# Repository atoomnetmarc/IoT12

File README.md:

# Hi!

This is an attempt at creating a soldering iron controller that uses T12 tips for a soldering iron handle with GX12-5 connector (KSGER FX9501 Handle). The pinout of the GX12-5 connector should match [this table](#control-board-j5-to-gx12-5-connector).

The name IoT12 is a portmanteau of IoT (because this soldering iron controller is connected to the internet using WiFi) and T12 (the type of soldering iron tip).

Have a look at the different elements that make up this project:

- [3d models for the case](3d/)
- [firmware for the heat controller and main processor](firmware/)
- [schematic and pcb](hardware/)

# Status

**Experimental and incomplete. Do not replicate yet.**

**You should be present at all times when using this project in case something goes wrong.**

# Assembly

You will need to 3d print all the parts mentioned in [3d](3d/README.md) directory.

You will need the 3 PCBs mentioned in the [hardware](hardware/README.md) directory.

# Cable harness

You need to crimp some JST-XH connectors and an IDC cable. Except for the IDC cable, use a wire diameter that can carry 3A. I used 0.2mm² (24 AWG, RS PRO series stranded tinned copper conductor equipment wire with PVC insulation).

## Power supply J2 to power switch

Cut 2 pieces of 14cm (5 33/64 inch) wire and crimp JST-XH pin on 1 end. Then plug into JST-XHP-2 connector. Solder the other end to a 16mm round rocker switch.

| Pin   | Description       | Wire color    |
| --:   | --                | --            |
| 1     | To power switch   | Purple        |
| 2     | To power switch   | Purple        |

## Power supply J3 to Control Board J4

Cut 4 pieces of 14cm wire and crimp JST-XH pin on both ends. Then plug into JST-XHP-4 connector.

| Pin   | Description   | Wire color    |
| --:   | --            | --            |
| 1     | +24V          | Yellow        |
| 2     | +5V           | Red           |
| 3     | GND           | Black         |
| 4     | +24V ON       | Pink          |

## Control board J2 to speaker

Cut 2 pieces of 14cm wire and crimp JST-XH pin on 1 end. Then plug into JST-XHP-2 connector. Solder the other end to a 4cm speaker (4 ohm 3 watt)

| Pin   | Description       | Wire color    |
| --:   | --                | --            |
| 1     | To speaker        | Brown         |
| 2     | To speaker        | Brown         |

## Control board J5 to GX12-5 connector

Cut 5 pieces of 14cm wire and crimp JST-XH pin on 1 end. Then plug into JST-XHP-52 connector. Solder other end to GX12-5 connector.

| Pin   | Description       | Wire color    |
| --:   | --                | --            |
| 1     | shake             | Blue          |
| 2     | NTC               | White         |
| 3     | ESD               | Green         |
| 4     | T12-              | Black         |
| 5     | T12+              | Red           |

## Control board J1 to Display Adapter J1

Cut a 14 cm 14-pin 1.27mm pitch ribbon cable. Crimp a IDC-14 connector on both ends. You should orient both connectors so that one polarizing key points away from the center of the cable and the other points to the center of the cable. Please note that pin 1 of the cable should align with pin 1 on both connectors (indicated by a triangle on the connector).

# Testing

Connect a (KSGER) T12 solder iron handle with the T12 tip (really) firmly seated inside to the GX12-5 socket. The JST-XH connector should connected to the control pcb. The power supply board should be connected to to the control pcb, but not powered on.

Measure about 60kΩ between the tip of the iron and GND on the control board (J6).

Measure 1MΩ between the tip of the iron and EARTH pin at the Power supply board (J1).

Now measure some values at the solder iron connector J5.\
The heater resistor between 4 (black) and 5 (red): 8Ω.\
Not 8Ω? Now retry and really push in the T12 tip into the handle.

Switch over to measure mV and measure 4 (black) and 5 (red) again. When you have not touched the handle and tip for half an hour you should read 0mV. Grab the cold T12 tip with your hand. You should notice an increasing voltage, possibly a rise until 0.1mV. It is possible your voltmeter is not capable of measuring in the microvolt range. You can heat the tip with a flame for a few seconds to increase the voltage some more.

Measure the NTC between 4 (black) and 2 (white): 5KΩ at 22°C (71.6°F) room temperature, but resistance could vary slightly when not measuring at 22°C.

Test the tilt sensor. Point soldering iron up and measure between 1 (blue) and 3 (green). You are measuring around 250kΩ.\
Point iron down and measure a low resistance of less than 100Ω.

The soldering iron handle is now validated to be correctly connected and should function correctly.

Connect the speaker to J2 on the control board.

Connect the power switch to J2 on the power supply board.

Connect display adapter J1 to control board J1.

Modules A1 and A3 should not be plugged in yet. All other connectors are plugged in.

Apply current limited (100mA) 24V with your lab power supply to the right leg of F1 on the power supply board (and gnd on some other pin like the middle pin of U1). Apply the 24V slowly starting at 0V. Stop at 6V. Measure the 5V pin on J4 (it should be 5.2V), notice LED D4 also lit up. Continue increasing to 24V. Current should stay below 10mA. Turn off lab power supply.

When all tests went well flash [the firmware](firmware/README.md) to both A1 (ESP32) and A3 (SAMD21). Do not plug in the modules in the control board before flashing the firmware.

Plug in A1 and A3. Both USB connectors should point to the center of the control board.
Again apply current limited 24V. But now increase the limit to 250mA. At about 6V the display should turn on. Both blue LEDs on A3 and the red LED on A3 should also light up. Current is now about 200mA. Increase until 24V. Current is now about 60mA.\
Measure the 3V3 pin on J6, it should measure 3.3V.

If your power supply can handle 3.5A at 24V you could try enable heating of the soldering iron. To enable heating you must switch on the power switch connected to J2 on the power supply board.

If you came this far and all tests went well, go reward yourself with your favorite drink or snack. Happy.

# Final assembly

\<insert final assembly instructions here, something about fitting everything in the 3d printed case, hmm, maybe this is all the instuctions needed>

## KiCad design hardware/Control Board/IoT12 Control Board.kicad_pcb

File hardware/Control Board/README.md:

# Assembly instructions

Use the [interactive BOM](bom/ibom.html) to identify values and positions of the components.

Solder all small 0805 SMD resistors and capacitors.
Read special instructions for R60, R61 and R62, R63 in the schematic.

Measure all resistors and check if they are all the correct resistance.

Solder rest of SMD components.

Clean PCB.

Inspect PCB with microscope for shorted pins (in ICs). Correct when found.

Solder all through-hole components.

Clean PCB.

You now have something like this:

Apply current limited 5V to GND and +5V on J4. Almost no current should flow.

Apply current limited 3.3V to GND and 3V3 on J6. Almost no current should flow.

# Done

Done!

# Pinout J1, Board-to-board Display

Connector to the Display Adapter. Direction seen from the control board.

| Pin# | Description | Direction |
| ---- | ----------- | --------- |
| 1    | +3.3V       | Power     |
| 2    | TFT_DC      | Out       |
| 3    | GND         | Power     |
| 4    | TFT_SCLK    | Out       |
| 5    | GND         | Power     |
| 6    | TFT_MOSI    | Out       |
| 7    | GND         | Power     |
| 8    | TFT_MISO    | In        |
| 9    | GND         | Power     |
| 10   | TFT_CS      | Out       |
| 11   | TFT_LED     | Out       |
| 12   | TFT_RST     | Out       |
| 13   | TOUCH_CS    | Out       |
| 14   | TOUCH_IRQ   | In        |

# Pinout J2, Speaker

Spoken soldering instructions for the visually impaired.

| Pin # | Description |
| ----- | ----------- |
| 1     | Loudspeaker |
| 2     | Loudspeaker |

# Pinout J4, Board-to-board Power

Goes to power board.

| Pin # | Description        |
| ----- | ------------------ |
| 1     | 24V switched power |
| 2     | 5V always on       |
| 3     | GND                |
| 4     | 24V_ON             |

# Pinout J5, T12 soldering iron

| Pin # | Description                      |
| ----- | -------------------------------- |
| 1     | SHAKE_IN                         |
| 2     | NTC_IN                           |
| 3     | ESD, connected with 100KΩ to GND |
| 4     | IRON\_-                          |
| 5     | IRON\_+                          |

# Pinout J6, Expansion I/O

Expansion connector, wired to the SAMD21 (EXP_D5, EXP_D7, EXP_SCL, EXP_SDA). Currently unused.

| Pin # | Description |
| ----- | ----------- |
| 1     | EXP_D5      |
| 2     | EXP_D7      |
| 3     | EXP_SCL     |
| 4     | EXP_SDA     |
| 5     | +3.3V       |
| 6     | GND         |

# Pinout A1, ESP32

The wireless brains.

| GPIO # | Description | Direction |
| ------ | ----------- | --------- |
| EN     | ESP32_RESET | In        |
| IO32   | TFT_LED     | Out       |
| IO33   | I2S_SD      | Out       |
| IO25   | I2S_BCK     | Out       |
| IO26   | I2S_WS      | Out       |
| IO21   | ESP32_SDA   | Bidir     |
| IO22   | ESP32_SCL   | Out       |
| IO14   | I2S_GAIN1   | Out       |
| IO13   | I2S_GAIN0   | Out       |
| IO15   | TFT_CS      | Out       |
| IO2    | TFT_DC      | Out       |
| IO4    | TFT_RST     | Out       |
| IO5    | TOUCH_CS    | Out       |
| IO18   | TFT_SCLK    | Out       |
| IO19   | TFT_MISO    | In        |
| IO23   | TFT_MOSI    | Out       |
| IO27   | I2S_DATA    | Out       |
| IO34   | TOUCH_IRQ   | In        |
| IO35   | HEAT_INT    | In        |

# Pinout A3, SAMD21

Heater controller

| GPIO #    | Description  | Direction |
| --------- | ------------ | --------- |
| RESET     | SAMD21_RESET | In        |
| PA02      | NTC          | In        |
| PB08      | TEMP         | In        |
| PB09+PA04 | SHAKE        | In        |
| PA05      | VIN          | In        |
| PB02      | IRON_CURRENT | In        |
| PA14      | HEAT_INT     | Out       |
| PA15      | EXP_D5       | Bidir     |
| PA20      | FLASH_CS     | Out       |
| PA21      | EXP_D7       | Bidir     |
| PA06      | ADC_RDY      | In        |
| PA07      | 24V_ON       | Out       |
| PA18      | HEAT_PWM     | Out       |
| PA22      | HEAT_SDA     | Bidir     |
| PA23      | HEAT_SCL     | Out       |
| PA08      | ESP32_SDA    | Bidir     |
| PA09      | ESP32_SCL    | In        |
| PA16      | EXP_SDA      | Bidir     |
| PA17      | EXP_SCL      | Out       |
| PA12      | MISO         | In        |
| PB11      | SCK          | Out       |
| PB10      | MOSI         | Out       |

# Pinout U2, ADS1115

16b I2C ADC, I2C address 0x48, on the HEAT I2C bus.

| Pin # | Pin name  | Description  | Direction |
| ----- | --------- | ------------ | --------- |
| 1     | ADDR      | GND          | In        |
| 2     | ALERT/RDY | ADC_RDY      | Out       |
| 3     | GND       | NEAR_ADC_GND | In        |
| 4     | AIN0      | TEMP         | In        |
| 5     | AIN1      | NTC          | In        |
| 6     | AIN2      | IRON_CURRENT | In        |
| 7     | AIN3      | VIN          | In        |
| 8     | VDD       | +3.3V        | In        |
| 9     | SDA       | HEAT_SDA     | Bidir     |
| 10    | SCL       | HEAT_SCL     | In        |

# Changelog

**Control board PCB version V2.2**

- Removed debug LED
- Removed 5110 LCD
- Removed rotary encoder
- Added header for 2.8" ILI9341 320x240 touch TFT
- Added relay for switching 24V
- Moved power supply circuitry to power supply PCB
- Removed small EEPROM
- Added SPI flash
- Added expansion header
- Layed out PCB again to fit on bottom lid of enclosure

**Control board PCB version V2.1**

- Swapped SDA/SCL I2C minion pins on heater controller.
- Swapped SDA/SCL I2C master pins on heater controller.
- Renamed PWM_HEAT to HEAT_PWM.
- Re-added MAX809S voltage monitor to keep ESP32 in reset if 3.3V is too low.
- Dimensioned F1 to 50% of Amax of T12-tip, see notes in schematic.
- Connected Vin ADC to after F1.
- Moved USB connector and reset button of heater controller.

**Control board PCB version V2.0**

- Replace safety features by microcontroller.
- Heating control now done by microcontroller.
- Changed shape and layout of pcb.

**Control board PCB version V1.1**

- Added explanation to schematic about using matched resistors for the instrumentation amplifiers.
- Changed gain resistors of the instrumentation amplifiers as to keep Vout under 1V at full scale input.
- Added series diode to output of voltage monitor.
- Lowered value of C2-C5 from 10nF to 1nF.
- Added D9 and D10.
- Changed value of R9 from 100R to 1k
- Added circuit to shutdown heating in case of overheating tip.

**Control board PCB version V1.0**

- First version that got made into PCB form.

# Eratta

**Control board PCB version V2.2**

No known erratum.

**Control board PCB version V2.1**

- It seems that after some use the 5110 LCD module has unreliable contacts. The LCD should be replaced by something else. PCB will need to be redesigned.
- A single occurrence of incorrect and fluctuating temperatures has been observed. Possibly caused by arcs in the power switch during power on. The power switch needs te be replaced by something else. Also the firmware needs to be made aware somehow of the situation and shutdown heating.

**Control board PCB version V2.0**

- I2C to heater controller not working. SDA/SCL are swapped. Swap them on the PCB near R55 and R56 to make the ESP32 communicate to the heater controller.
- A theme is developing :unamused:. I2C from the heater controller to the I2C EEPROM and ADC is not working. SDA/SCL are swapped. Swap them between R53, R54 and the heater controller on the bottom where the SDA/SCL traces run next to each other.
- ESP32 will lockup if power supply rise time is too slow.

**Control board PCB version V1.1**

- Overheating protection circuit not very stable. No fix.

**Control board PCB version V1.0**

- Silkscreen error in 'Solder iron connector'-block. '5, red, +.' and '4, black, ground.' are switched resulting in negative voltages for positive temperatures. Switch leads will solve this. Corrected in next PCB version.
- Gain of instrumentation amplifiers not correct.
- Programming by USB is impossible.
- Measuring temperature takes too long (20ms).

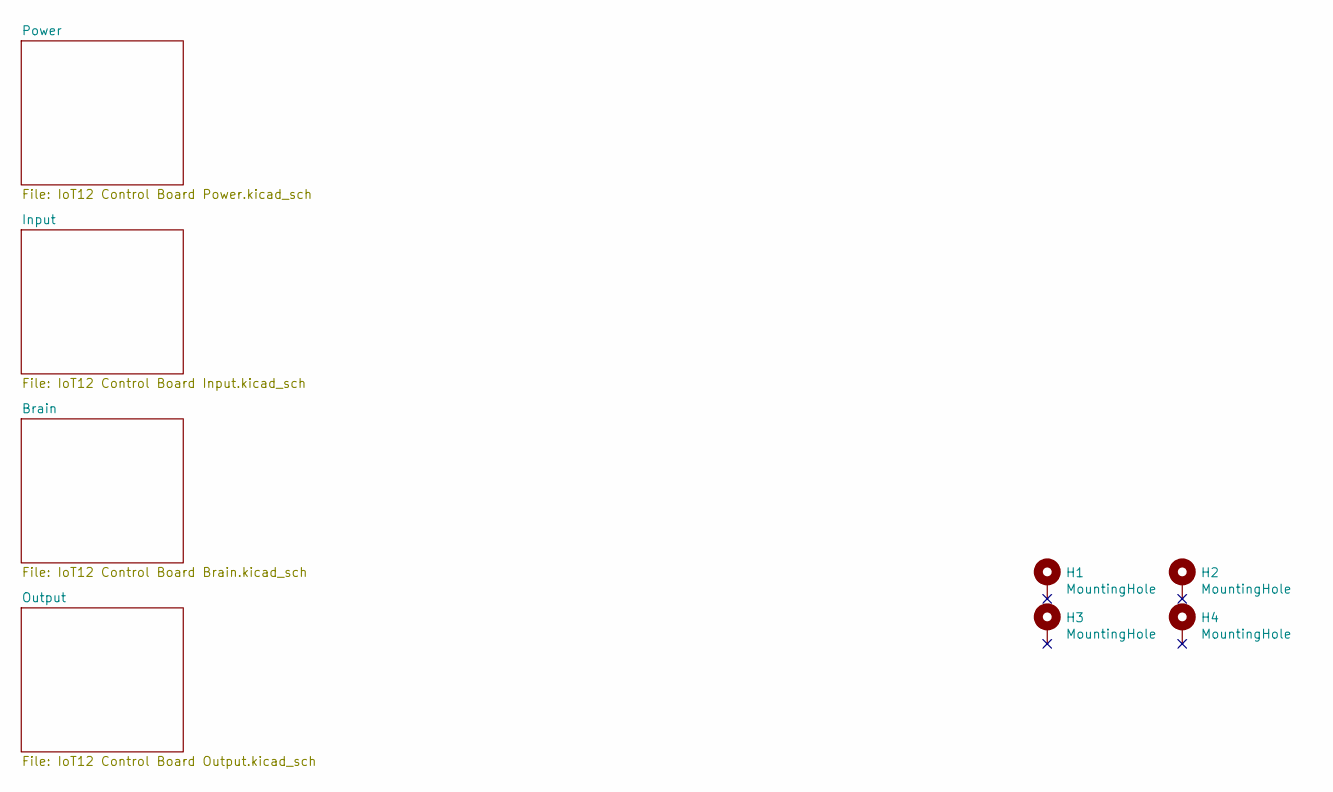
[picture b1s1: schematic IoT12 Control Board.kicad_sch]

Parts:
H1, H2, H3, H4: MountingHole; MountingHole_3.2mm_M3_Pad_Via

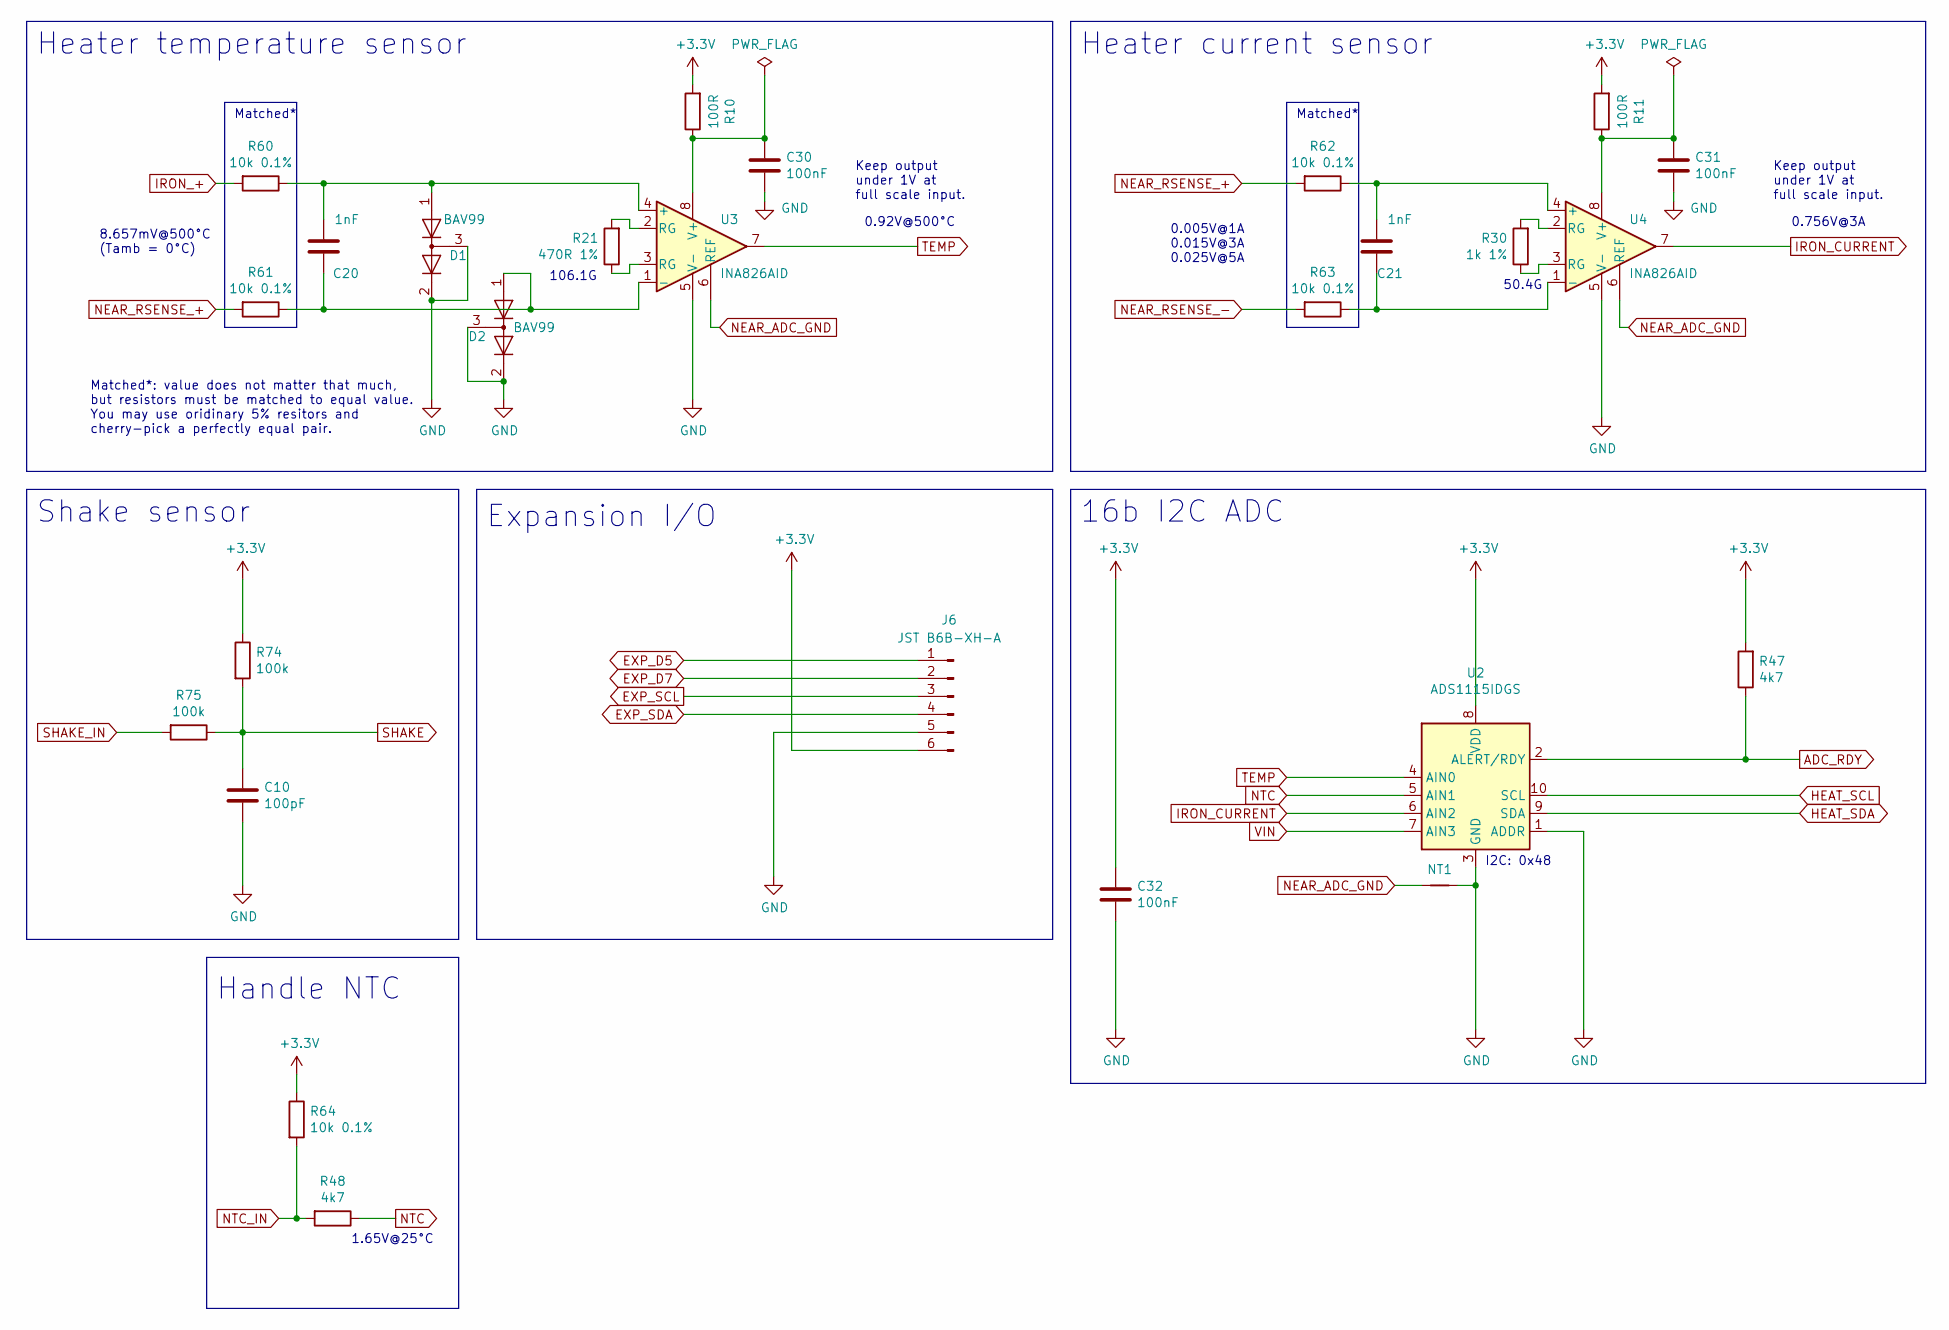
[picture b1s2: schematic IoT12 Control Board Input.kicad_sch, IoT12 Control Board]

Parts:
C10: 100pF; C_0805_2012Metric_Pad1.18x1.45mm_HandSolder
C20, C21: 1nF; C_0805_2012Metric_Pad1.18x1.45mm_HandSolder
C30, C31, C32: 100nF; C_0805_2012Metric_Pad1.18x1.45mm_HandSolder
D1, D2: BAV99; SOT-23
J6: JST B6B-XH-A; JST_XH_B6B-XH-A_1x06_P2.50mm_Vertical
NT1: NetTie-2_SMD_Pad0.5mm
R10, R11: 100R; R_0805_2012Metric_Pad1.20x1.40mm_HandSolder
R21: 470R 1%; R_0805_2012Metric_Pad1.20x1.40mm_HandSolder
R30: 1k 1%; R_0805_2012Metric_Pad1.20x1.40mm_HandSolder
R47, R48: 4k7; R_0805_2012Metric_Pad1.20x1.40mm_HandSolder
R60, R61, R62, R63, R64: 10k 0.1%; R_0805_2012Metric_Pad1.20x1.40mm_HandSolder
R74, R75: 100k; R_0805_2012Metric_Pad1.20x1.40mm_HandSolder
U2: ADS1115IDGS; TSSOP-10_3x3mm_P0.5mm
U3, U4: INA826AID; SOIC-8_5.23x5.23mm_P1.27mm

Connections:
+3.3V: C32.1, J6.6, R10.2, R11.2, R47.2, R64.1, R74.1, U2.8 (VDD); also elsewhere on the board
ADC_RDY: R47.1, U2.2 (ALERT/RDY); also elsewhere on the board
EXP_D5: J6.1; also elsewhere on the board
EXP_D7: J6.2; also elsewhere on the board
EXP_SCL: J6.3; also elsewhere on the board
EXP_SDA: J6.4; also elsewhere on the board
GND: C10.2, C30.2, C31.2, C32.2, D1.2 (A), D1.3 (K), D2.2 (A), D2.3 (K), J6.5, NT1.2, U2.1 (ADDR), U2.3 (GND), U3.5 (V-), U4.5 (V-); also elsewhere on the board
HEAT_SCL: U2.10 (SCL); also elsewhere on the board
HEAT_SDA: U2.9 (SDA); also elsewhere on the board
IRON_+: R60.2; also elsewhere on the board
IRON_CURRENT: U2.6 (AIN2), U4.7; also elsewhere on the board
NEAR_ADC_GND: NT1.1, U3.6 (REF), U4.6 (REF)
NEAR_RSENSE_+: R61.2, R62.2; also elsewhere on the board
NEAR_RSENSE_-: R63.2; also elsewhere on the board
NTC: R48.1, U2.5 (AIN1); also elsewhere on the board
NTC_IN: R48.2, R64.2; also elsewhere on the board
unnamed: C30.1, R10.1, U3.8 (V+)
unnamed: C31.1, R11.1, U4.8 (V+)
unnamed: R21.1, U3.3 (RG)
unnamed: R21.2, U3.2 (RG)
unnamed: R30.1, U4.3 (RG)
unnamed: R30.2, U4.2 (RG)
unnamed: C20.1, D1.1 (K), R60.1, U3.4 (+)
unnamed: C20.2, D2.1 (K), R61.1, U3.1 (-)
unnamed: C21.1, R62.1, U4.4 (+)
unnamed: C21.2, R63.1, U4.1 (-)
SHAKE: C10.1, R74.2, R75.1; also elsewhere on the board
SHAKE_IN: R75.2; also elsewhere on the board
TEMP: U2.4 (AIN0), U3.7; also elsewhere on the board
VIN: U2.7 (AIN3); also elsewhere on the board

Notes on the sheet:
I2C: 0x48
50.4G
0.005V@1A 0.015V@3A 0.025V@5A
8.657mV@500°C (Tamb = 0°C)
Heater temperature sensor
Matched*: value does not matter that much, but resistors must be matched to equal value. You may use oridinary 5% resitors and cherry-pick a perfectly equal pair.
Matched*
106.1G
0.756V@3A
Shake sensor
0.92V@500°C
16b I2C ADC
Expansion I/O
Keep output under 1V at full scale input.
Heater current sensor
1.65V@25°C
Handle NTC

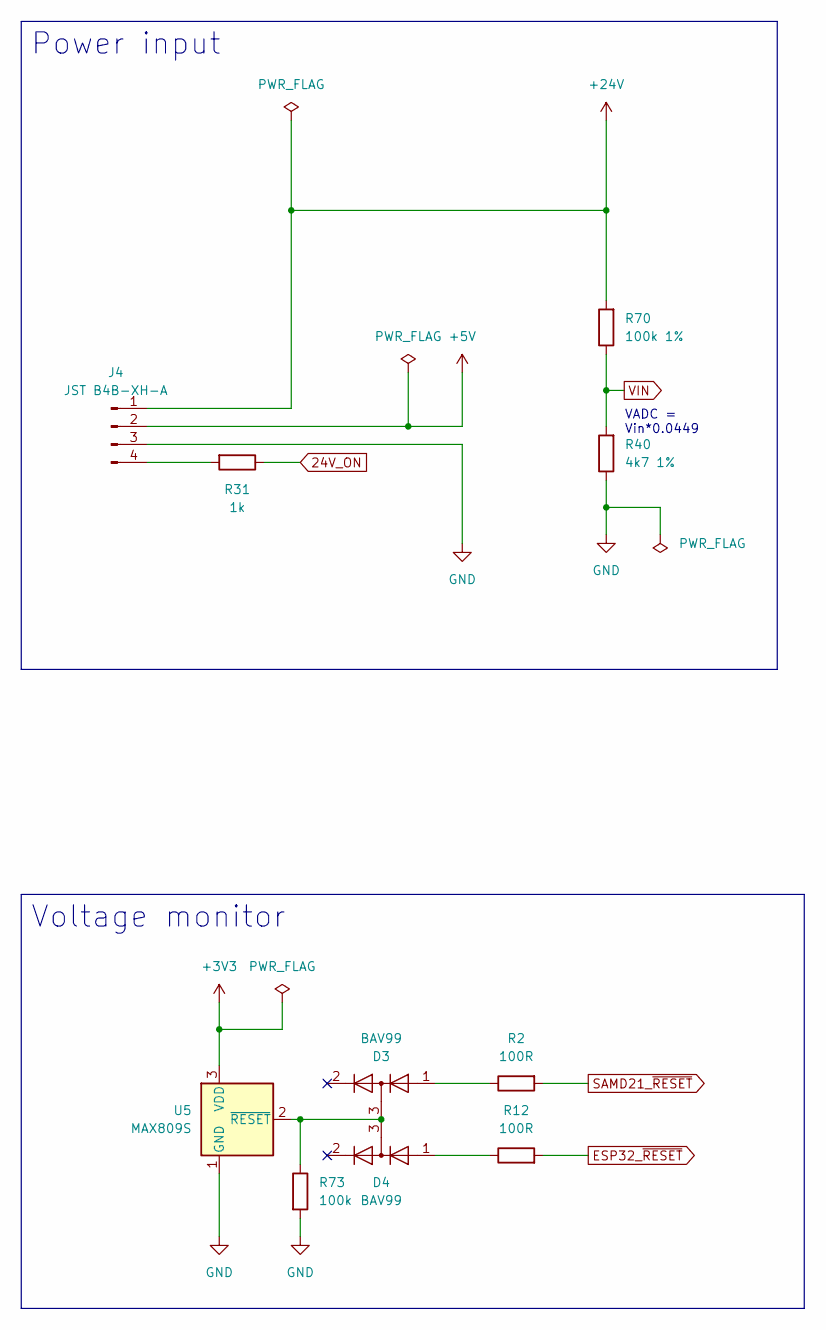
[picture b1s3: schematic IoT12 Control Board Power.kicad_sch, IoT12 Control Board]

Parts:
D3, D4: BAV99; SOT-23
J4: JST B4B-XH-A; JST_XH_B4B-XH-A_1x04_P2.50mm_Vertical
R2, R12: 100R; R_0805_2012Metric_Pad1.20x1.40mm_HandSolder
R31: 1k; R_0805_2012Metric_Pad1.20x1.40mm_HandSolder
R40: 4k7 1%; R_0805_2012Metric_Pad1.20x1.40mm_HandSolder
R70: 100k 1%; R_0805_2012Metric_Pad1.20x1.40mm_HandSolder
R73: 100k; R_0805_2012Metric_Pad1.20x1.40mm_HandSolder
U5: MAX809S; SOT-23

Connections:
24V_ON: R31.1; also elsewhere on the board
+3V3: U5.3 (VDD)
+5V: J4.2; also elsewhere on the board
+24V: J4.1, R70.2; also elsewhere on the board
ESP32_~RESET: R12.2; also elsewhere on the board
GND: J4.3, R40.1, R73.2, U5.1 (GND); also elsewhere on the board
unnamed: D3.1 (K), R2.1
unnamed: D4.1 (K), R12.1
unnamed: J4.4, R31.2
unnamed: D3.3 (K), D4.3 (K), R73.1, U5.2 (~RESET)
SAMD21_~RESET: R2.2; also elsewhere on the board
VIN: R40.2, R70.1; also elsewhere on the board

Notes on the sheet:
Power input
VADC = Vin*0.0449
Voltage monitor

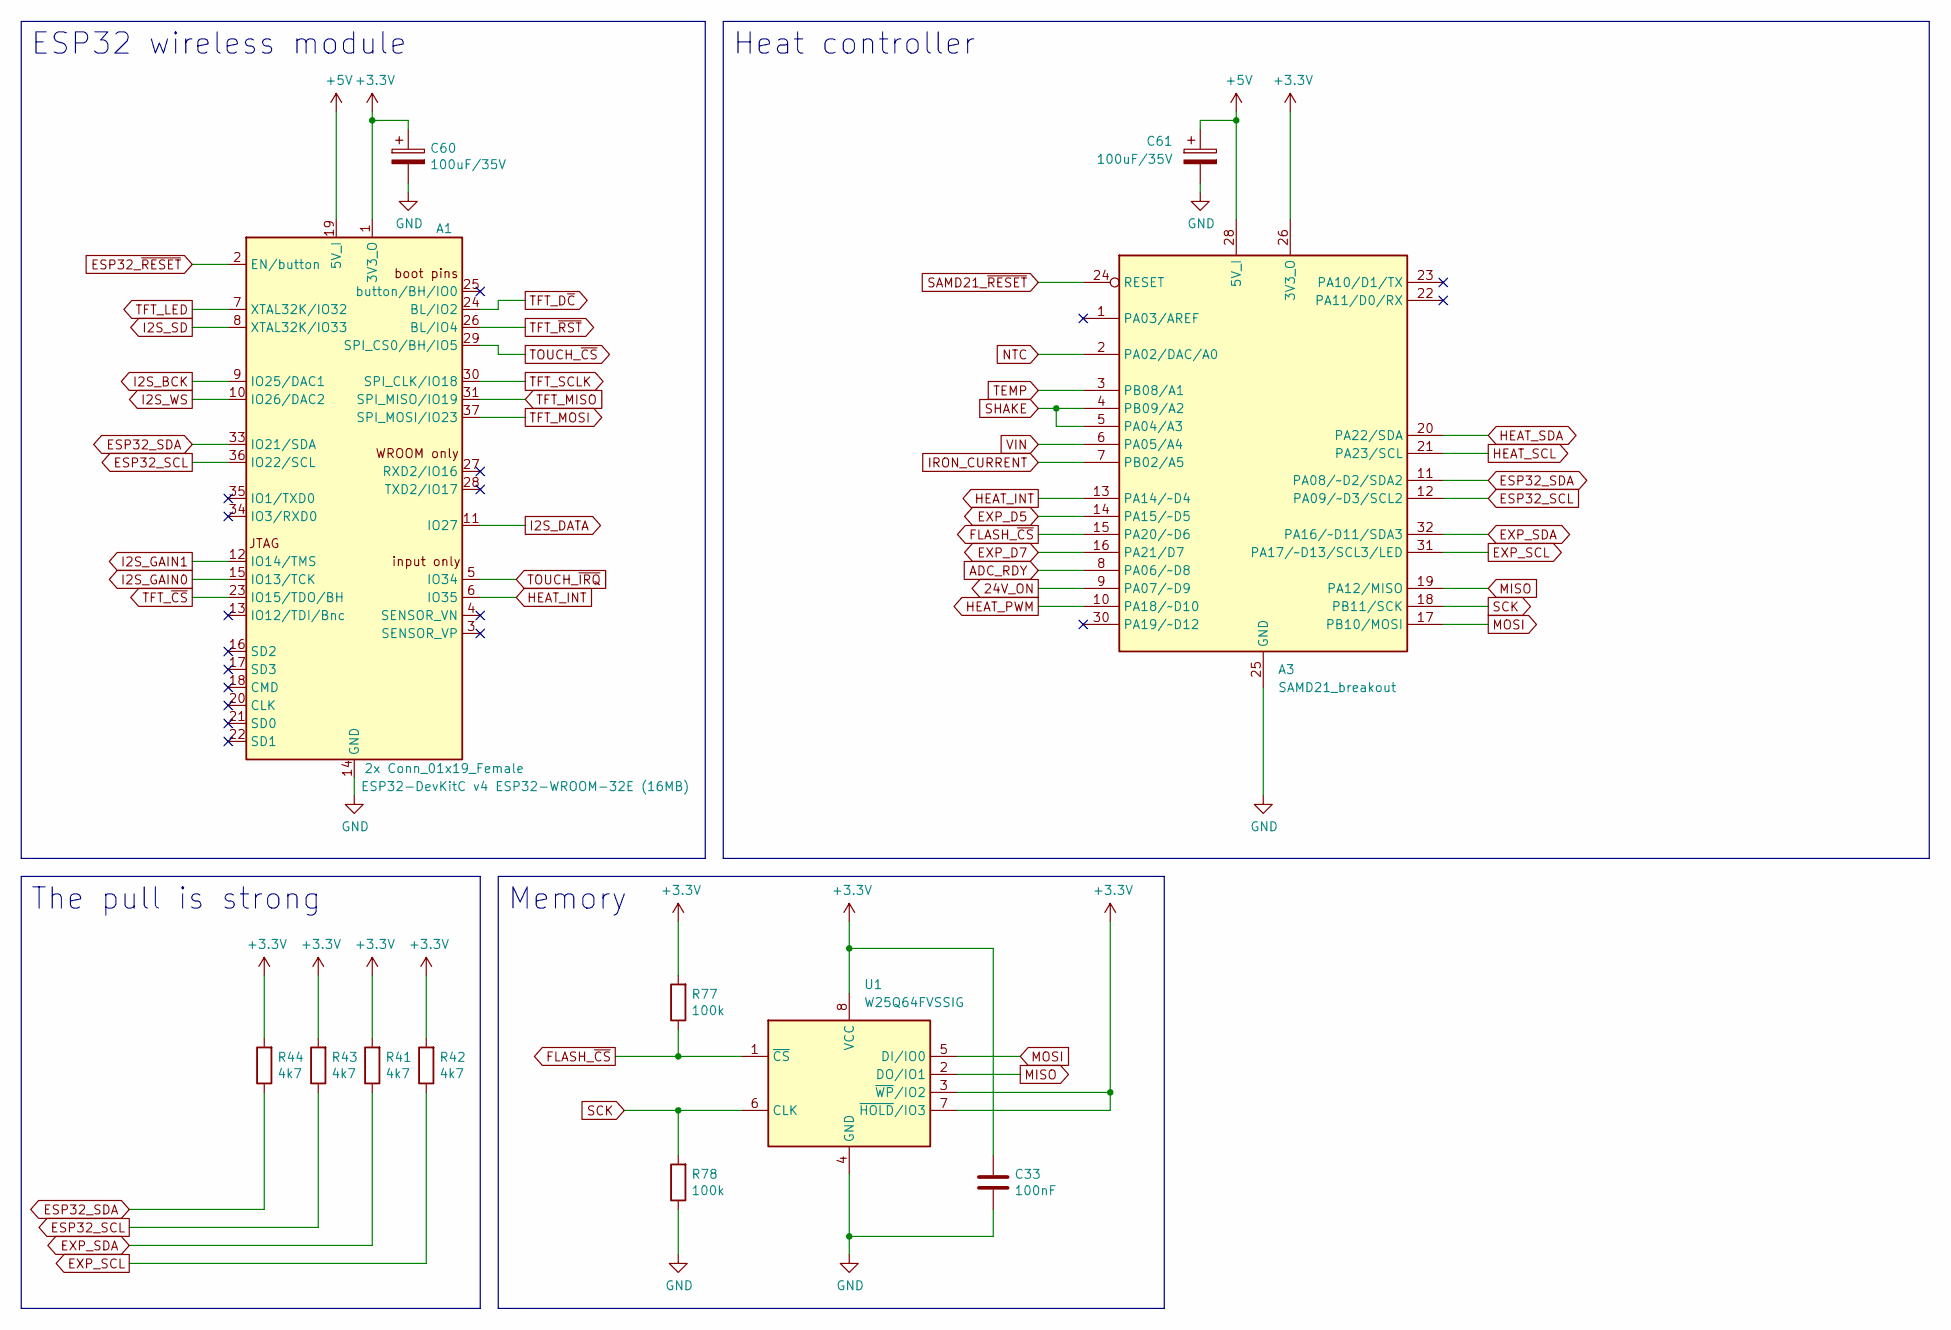
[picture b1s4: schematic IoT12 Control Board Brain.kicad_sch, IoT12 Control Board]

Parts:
A1: 2x Conn_01x19_Female; ESP32-DevKitC
A3: SAMD21_breakout
C33: 100nF; C_0805_2012Metric_Pad1.18x1.45mm_HandSolder
C60, C61: 100uF/35V; CP_Elec_6.3x7.7
R41, R42, R43, R44: 4k7; R_0805_2012Metric_Pad1.20x1.40mm_HandSolder
R77, R78: 100k; R_0805_2012Metric_Pad1.20x1.40mm_HandSolder
U1: W25Q64FVSSIG; SOIC-8_5.23x5.23mm_P1.27mm

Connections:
24V_ON: A3.9 (PA07/~D9); also elsewhere on the board
+3.3V: A1.1 (3V3_O), A3.26 (3V3_O), C33.1, C60.1, R41.2, R42.2, R43.2, R44.2, R77.2, U1.3 (~WP/IO2), U1.7 (~HOLD/IO3), U1.8 (VCC); also elsewhere on the board
+5V: A1.19 (5V_I), A3.28 (5V_I), C61.1; also elsewhere on the board
ADC_RDY: A3.8 (PA06/~D8); also elsewhere on the board
ESP32_SCL: A1.36 (IO22/SCL), A3.12 (PA09/~D3/SCL2), R43.1
ESP32_SDA: A1.33 (IO21/SDA), A3.11 (PA08/~D2/SDA2), R44.1
ESP32_~RESET: A1.2 (EN/button); also elsewhere on the board
EXP_D5: A3.14 (PA15/~D5); also elsewhere on the board
EXP_D7: A3.16 (PA21/D7); also elsewhere on the board
EXP_SCL: A3.31 (PA17/~D13/SCL3/LED), R42.1; also elsewhere on the board
EXP_SDA: A3.32 (PA16/~D11/SDA3), R41.1; also elsewhere on the board
FLASH_~CS: A3.15 (PA20/~D6), R77.1, U1.1 (~CS)
GND: A1.14 (GND), A1.32 (GND), A1.38 (GND), A3.25 (GND), A3.29 (GND), C33.2, C60.2, C61.2, R78.1, U1.4 (GND); also elsewhere on the board
HEAT_INT: A1.6 (IO35), A3.13 (PA14/~D4)
HEAT_PWM: A3.10 (PA18/~D10); also elsewhere on the board
HEAT_SCL: A3.21 (PA23/SCL); also elsewhere on the board
HEAT_SDA: A3.20 (PA22/SDA); also elsewhere on the board
I2S_BCK: A1.9 (IO25/DAC1); also elsewhere on the board
I2S_DATA: A1.11 (IO27); also elsewhere on the board
I2S_GAIN0: A1.15 (IO13/TCK); also elsewhere on the board
I2S_GAIN1: A1.12 (IO14/TMS); also elsewhere on the board
I2S_SD: A1.8 (XTAL32K/IO33); also elsewhere on the board
I2S_WS: A1.10 (IO26/DAC2); also elsewhere on the board
IRON_CURRENT: A3.7 (PB02/A5); also elsewhere on the board
MISO: A3.19 (PA12/MISO), U1.2 (DO/IO1)
MOSI: A3.17 (PB10/MOSI), U1.5 (DI/IO0)
NTC: A3.2 (PA02/DAC/A0); also elsewhere on the board
SAMD21_~RESET: A3.24 (RESET); also elsewhere on the board
SCK: A3.18 (PB11/SCK), R78.2, U1.6 (CLK)
SHAKE: A3.4 (PB09/A2), A3.5 (PA04/A3); also elsewhere on the board
TEMP: A3.3 (PB08/A1); also elsewhere on the board
TFT_D~C: A1.24 (BL/IO2); also elsewhere on the board
TFT_LED: A1.7 (XTAL32K/IO32); also elsewhere on the board
TFT_MISO: A1.31 (SPI_MISO/IO19); also elsewhere on the board
TFT_MOSI: A1.37 (SPI_MOSI/IO23); also elsewhere on the board
TFT_SCLK: A1.30 (SPI_CLK/IO18); also elsewhere on the board
TFT_~CS: A1.23 (IO15/TDO/BH); also elsewhere on the board
TFT_~RST: A1.26 (BL/IO4); also elsewhere on the board
TOUCH_~CS: A1.29 (SPI_CS0/BH/IO5); also elsewhere on the board
TOUCH_~IRQ: A1.5 (IO34); also elsewhere on the board
VIN: A3.6 (PA05/A4); also elsewhere on the board

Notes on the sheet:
The pull is strong
Memory
Heat controller
ESP32 wireless module

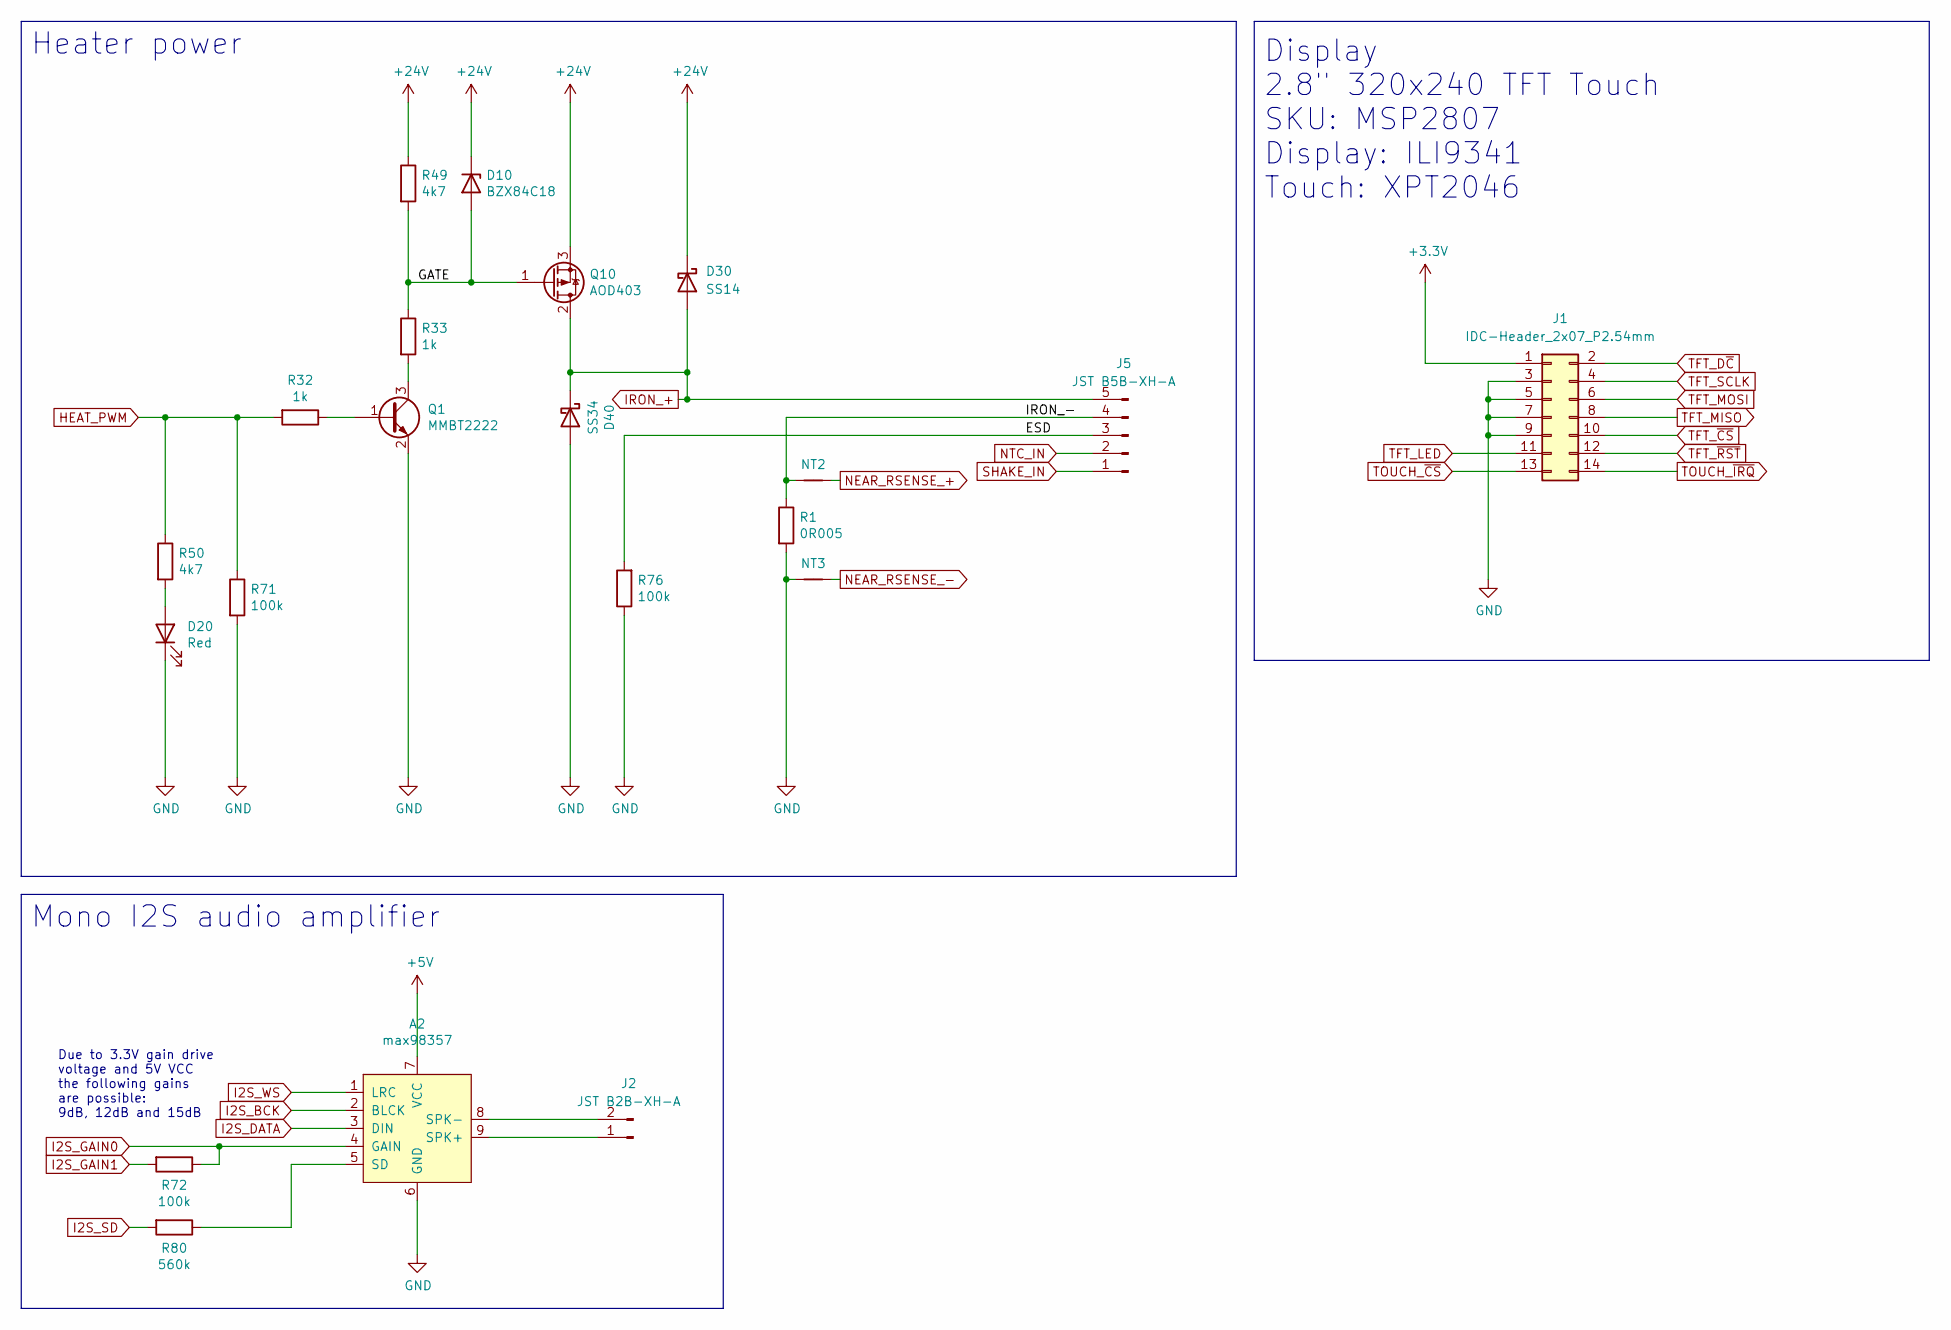
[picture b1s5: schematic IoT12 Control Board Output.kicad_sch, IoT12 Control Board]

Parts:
A2: max98357
D10: BZX84C18; SOT-23
D20: Red; LED_0805_2012Metric_Pad1.15x1.40mm_HandSolder
D30: SS14; D_SMA
D40: SS34; D_SMA
J1: IDC-Header_2x07_P2.54mm; IDC-Header_2x07_P2.54mm_Vertical
J2: JST B2B-XH-A; JST_XH_B2B-XH-A_1x02_P2.50mm_Vertical
J5: JST B5B-XH-A; JST_XH_B5B-XH-A_1x05_P2.50mm_Vertical
NT2, NT3: NetTie-2_SMD_Pad0.5mm
Q1: MMBT2222; SOT-23
Q10: AOD403; TO-252-2
R1: 0R005; R_2512_6332Metric_Pad1.40x3.35mm_HandSolder
R32, R33: 1k; R_0805_2012Metric_Pad1.20x1.40mm_HandSolder
R49, R50: 4k7; R_0805_2012Metric_Pad1.20x1.40mm_HandSolder
R71, R72, R76: 100k; R_0805_2012Metric_Pad1.20x1.40mm_HandSolder
R80: 560k; R_0805_2012Metric_Pad1.20x1.40mm_HandSolder

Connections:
+3.3V: J1.1; also elsewhere on the board
+5V: A2.7 (VCC); also elsewhere on the board
+24V: D10.3 (K), D30.1 (K), Q10.3 (S), R49.1; also elsewhere on the board
/Output/ESD: J5.3, R76.2
/Output/GATE: D10.1 (A), Q10.1 (G), R33.1, R49.2
/Output/IRON_-: J5.4, NT2.1, R1.1
GND: A2.6 (GND), D20.1 (K), D40.2 (A), J1.3, J1.5, J1.7, J1.9, NT3.1, Q1.2 (E), R1.2, R71.2, R76.1; also elsewhere on the board
HEAT_PWM: R32.2, R50.1, R71.1; also elsewhere on the board
I2S_BCK: A2.2 (BLCK); also elsewhere on the board
I2S_DATA: A2.3 (DIN); also elsewhere on the board
I2S_GAIN0: A2.4 (GAIN), R72.1; also elsewhere on the board
I2S_GAIN1: R72.2; also elsewhere on the board
I2S_SD: R80.2; also elsewhere on the board
I2S_WS: A2.1 (LRC); also elsewhere on the board
IRON_+: D30.2 (A), D40.1 (K), J5.5, Q10.2 (D); also elsewhere on the board
NEAR_RSENSE_+: NT2.2; also elsewhere on the board
NEAR_RSENSE_-: NT3.2; also elsewhere on the board
NTC_IN: J5.2; also elsewhere on the board
unnamed: A2.5 (SD), R80.1
unnamed: A2.9 (SPK+), J2.1
unnamed: A2.8 (SPK-), J2.2
unnamed: D20.2 (A), R50.2
unnamed: Q1.1 (B), R32.1
unnamed: Q1.3 (C), R33.2
SHAKE_IN: J5.1; also elsewhere on the board
TFT_D~C: J1.2; also elsewhere on the board
TFT_LED: J1.11; also elsewhere on the board
TFT_MISO: J1.8; also elsewhere on the board
TFT_MOSI: J1.6; also elsewhere on the board
TFT_SCLK: J1.4; also elsewhere on the board
TFT_~CS: J1.10; also elsewhere on the board
TFT_~RST: J1.12; also elsewhere on the board
TOUCH_~CS: J1.13; also elsewhere on the board
TOUCH_~IRQ: J1.14; also elsewhere on the board

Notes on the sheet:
Heater power
Due to 3.3V gain drive voltage and 5V VCC the following gains are possible: 9dB, 12dB and 15dB
Mono I2S audio amplifier
Display 2.8" 320x240 TFT Touch SKU: MSP2807 Display: ILI9341 Touch: XPT2046

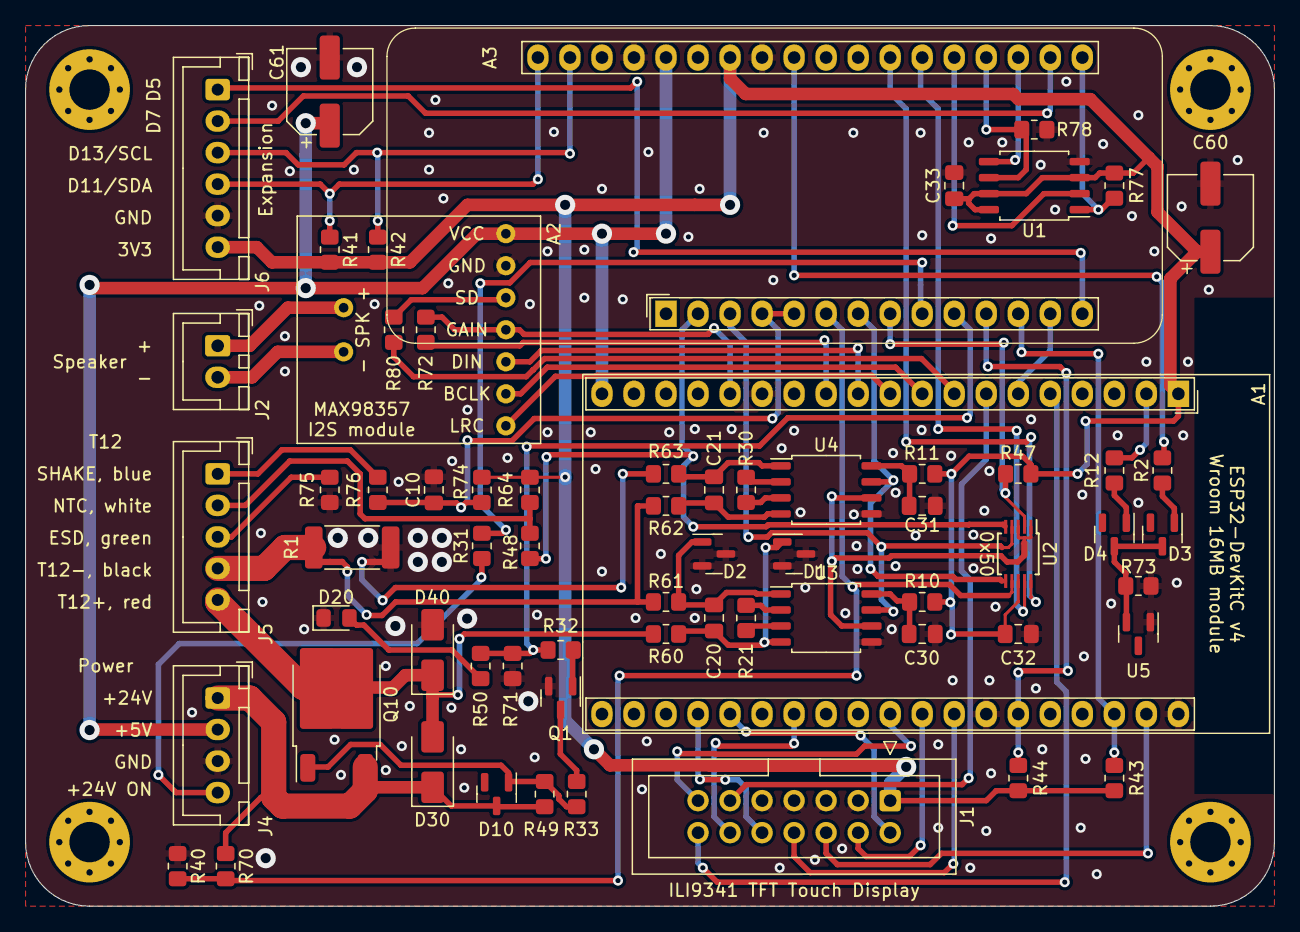
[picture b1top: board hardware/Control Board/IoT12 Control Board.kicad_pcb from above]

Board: 2 copper layers, 99.1 x 69.9 mm, 73 parts (0 on the bottom side), 71 nets.

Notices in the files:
Control Board/IoT12 Control Board.kicad_pcb:
Apache License, Version 2.0
Power Supply/README.md:
License: Apache 2.0
